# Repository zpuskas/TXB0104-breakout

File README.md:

# TXB0104 Breadboard Breakout

Breakout board for the TXB0104 bidirectional voltage-level translator IC with
automatic direction sensing. The main difference of this board compared to
[SparkFun's Voltage-Level Translator Breakout](https://www.sparkfun.com/products/11771)
is that the OE pin is independent, and not soldered to VCCA by default,
allowing for any side of the communication to be in control of the data flow
out of the box.

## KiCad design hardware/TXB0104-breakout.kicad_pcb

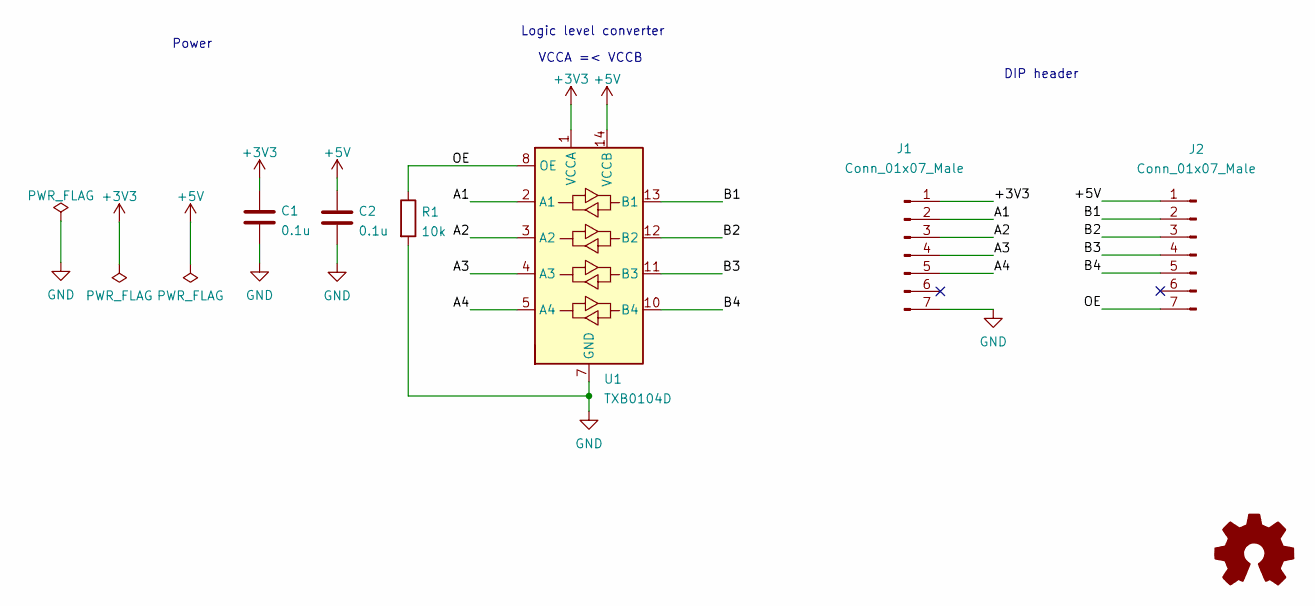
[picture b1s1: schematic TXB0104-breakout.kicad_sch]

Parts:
C1, C2: 0.1u; C_0805_2012Metric_Pad1.18x1.45mm_HandSolder
J1, J2: Conn_01x07_Male; PinHeader_1x07_P2.54mm_Vertical
R1: 10k; R_0805_2012Metric_Pad1.20x1.40mm_HandSolder
U1: TXB0104D; SOIC-14_3.9x8.7mm_P1.27mm

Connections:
+3V3: C1.1, J1.1, U1.1 (VCCA)
+5V: C2.1, J2.1, U1.14 (VCCB)
/A1: J1.2, U1.2 (A1)
/A2: J1.3, U1.3 (A2)
/A3: J1.4, U1.4 (A3)
/A4: J1.5, U1.5 (A4)
/B1: J2.2, U1.13 (B1)
/B2: J2.3, U1.12 (B2)
/B3: J2.4, U1.11 (B3)
/B4: J2.5, U1.10 (B4)
/OE: J2.7, R1.1, U1.8 (OE)
GND: C1.2, C2.2, J1.7, R1.2, U1.7 (GND)

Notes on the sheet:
VCCA =< VCCB
Power
DIP header
Logic level converter

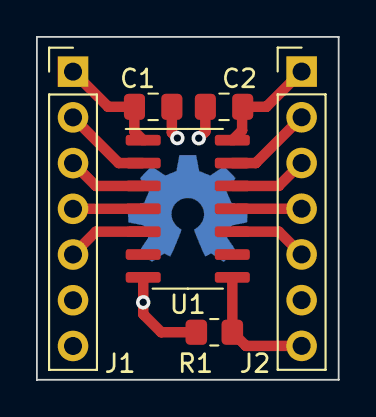
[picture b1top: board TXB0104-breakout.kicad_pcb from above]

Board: 2 copper layers, 16.8 x 19.1 mm, 7 parts (1 on the bottom side), 12 nets.

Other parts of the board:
REF1: OSHW-Symbol_6.7x6mm_Copper

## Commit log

2022-02-20 Add first version of the breakout board
    This breakout board uses a TXB0104 level converter chip, that can be
    used to match communication buses between circuits operating at
    different voltages.
2022-02-21 Add README to the repository
2022-03-06 Update board
    - add pull down resistor to output enable pin to ensure off state during
    power on
    - remove extra gound planes from the signal layer to reduce potential RF
    emissions from the board
    - fix bottom silk screen
2022-03-14 Fine tune PCB
    - Move ground vias for the bypass capacitors closer to power lines to
    reduce loop size
    - Update bottom silk screen text arrangement for more symmetry
